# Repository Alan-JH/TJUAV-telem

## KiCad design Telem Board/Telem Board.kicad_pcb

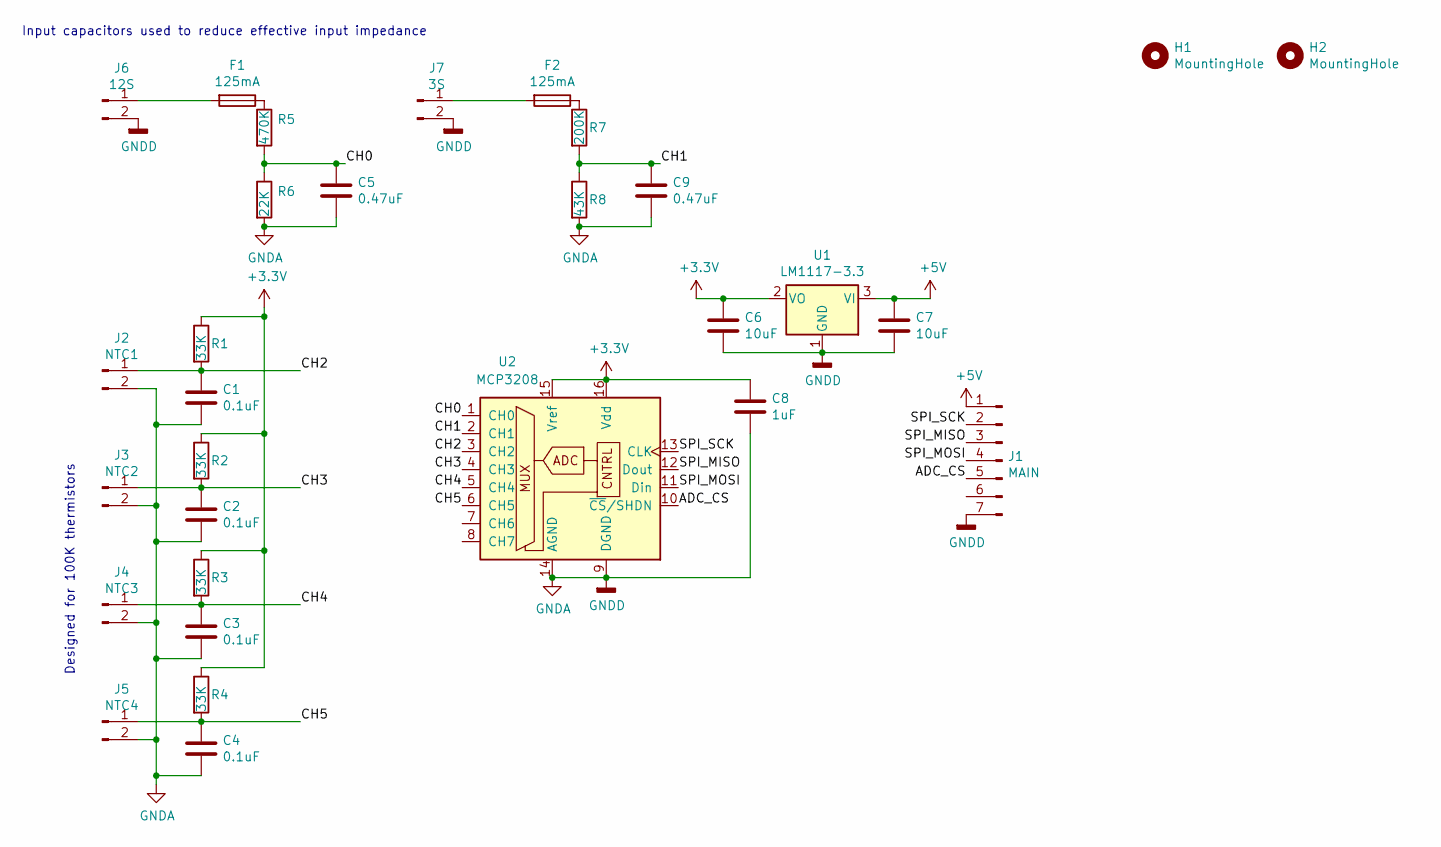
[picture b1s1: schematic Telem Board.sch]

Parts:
C1, C2, C3, C4: 0.1uF; C_0805_2012Metric_Pad1.18x1.45mm_HandSolder
C5, C9: 0.47uF; C_0805_2012Metric_Pad1.18x1.45mm_HandSolder
C6, C7: 10uF; C_0805_2012Metric_Pad1.18x1.45mm_HandSolder
C8: 1uF; C_0805_2012Metric_Pad1.18x1.45mm_HandSolder
F1, F2: 125mA; R_1206_3216Metric_Pad1.30x1.75mm_HandSolder
H1, H2: MountingHole; MountingHole_2.7mm_M2.5
J1: MAIN; PinHeader_1x07_P2.54mm_Vertical
J2: NTC1; PinHeader_1x02_P2.54mm_Vertical
J3: NTC2; PinHeader_1x02_P2.54mm_Vertical
J4: NTC3; PinHeader_1x02_P2.54mm_Vertical
J5: NTC4; PinHeader_1x02_P2.54mm_Vertical
J6: 12S; AMASS_XT60-M_1x02_P7.20mm_Vertical
J7: 3S; AMASS_XT60-M_1x02_P7.20mm_Vertical
R1, R2, R3, R4: 33K; C_1206_3216Metric_Pad1.33x1.80mm_HandSolder
R5: 470K; C_1206_3216Metric_Pad1.33x1.80mm_HandSolder
R6: 22K; C_1206_3216Metric_Pad1.33x1.80mm_HandSolder
R7: 200K; C_1206_3216Metric_Pad1.33x1.80mm_HandSolder
R8: 43K; C_1206_3216Metric_Pad1.33x1.80mm_HandSolder
U1: LM1117-3.3; SOT-223-3_TabPin2
U2: MCP3208; DIP-16_W7.62mm

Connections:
+3V3: C6.1, C8.1, R1.1, R2.1, R3.1, R4.1, U1.2 (VO), U2.15 (Vref), U2.16 (Vdd)
+5V: C7.1, J1.1, U1.3 (VI)
/ADC_CS: J1.5, U2.10 (~CS~/SHDN)
/CH0: C5.1, R5.2, R6.1, U2.1 (CH0)
/CH1: C9.1, R7.2, R8.1, U2.2 (CH1)
/CH2: C1.1, J2.1, R1.2, U2.3 (CH2)
/CH3: C2.1, J3.1, R2.2, U2.4 (CH3)
/CH4: C3.1, J4.1, R3.2, U2.5 (CH4)
/CH5: C4.1, J5.1, R4.2, U2.6 (CH5)
/SPI_MISO: J1.3, U2.12 (Dout)
/SPI_MOSI: J1.4, U2.11 (Din)
/SPI_SCK: J1.2, U2.13 (CLK)
GNDA: C1.2, C2.2, C3.2, C4.2, C5.2, C6.2, C7.2, C8.2, C9.2, J1.7, J2.2, J3.2, J4.2, J5.2, J6.2, J7.2, R6.2, R8.2, U1.1 (GND), U2.9 (DGND), U2.14 (AGND)
unnamed: F1.1, R5.1
unnamed: F1.2, J6.1
unnamed: F2.1, R7.1
unnamed: F2.2, J7.1

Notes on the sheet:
Designed for 100K thermistors
Input capacitors used to reduce effective input impedance

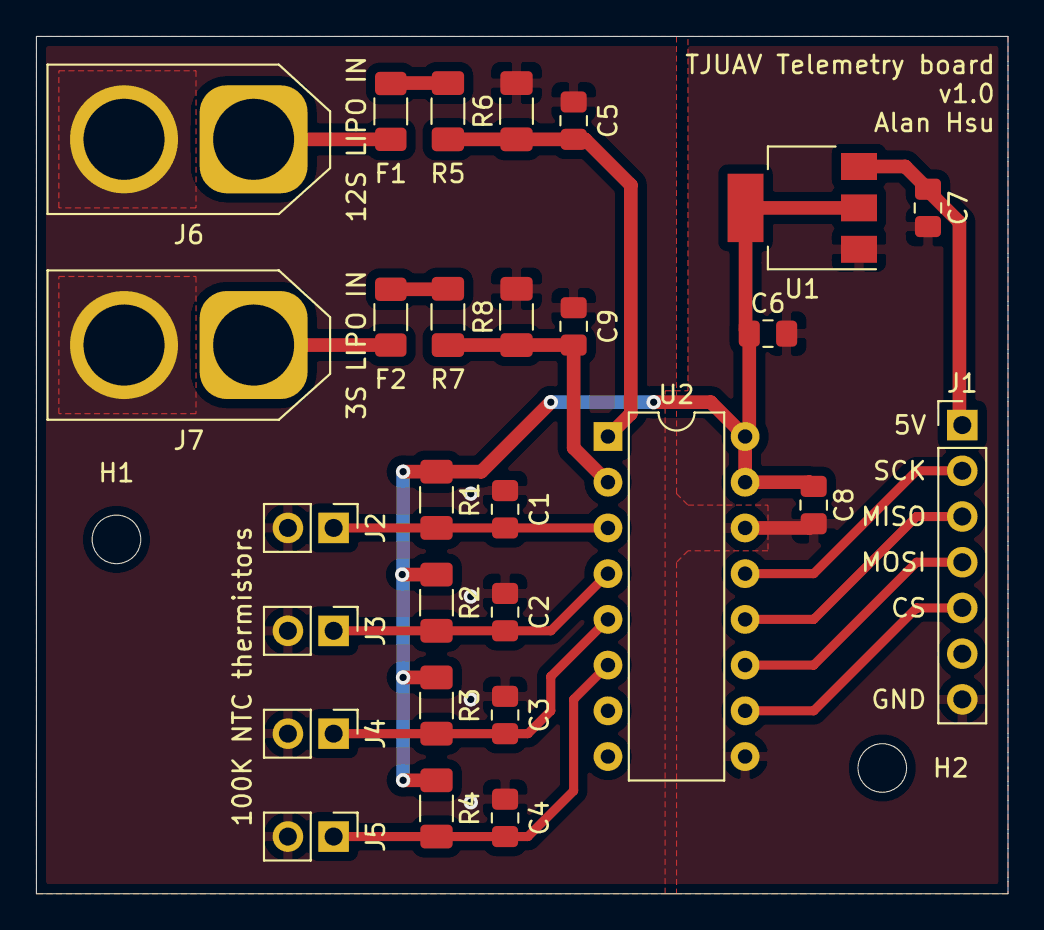
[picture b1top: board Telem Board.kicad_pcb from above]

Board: 2 copper layers, 54.0 x 47.6 mm, 30 parts (0 on the bottom side), 17 nets.

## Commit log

2021-11-14 finish sch
2021-11-14 route
2021-11-14 add 3s battery in
2021-11-15 gerbers
2021-11-15 use 12s resistor sizes instead of 6s
    #1
2021-11-18 update gerbers
2021-11-28 update values
